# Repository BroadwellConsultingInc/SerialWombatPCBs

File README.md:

# SerialWombatPCBs
Serial Wombat Board Designs and Documentation

This repository holds Eagle PCB designs, gerbers, schematics, and other documentation, code, templates, drawings, etc. related to Serial Wombat brand PCBs.

Serial Wombat is a registered trademark in the United States of Broadwell Consulting Inc.

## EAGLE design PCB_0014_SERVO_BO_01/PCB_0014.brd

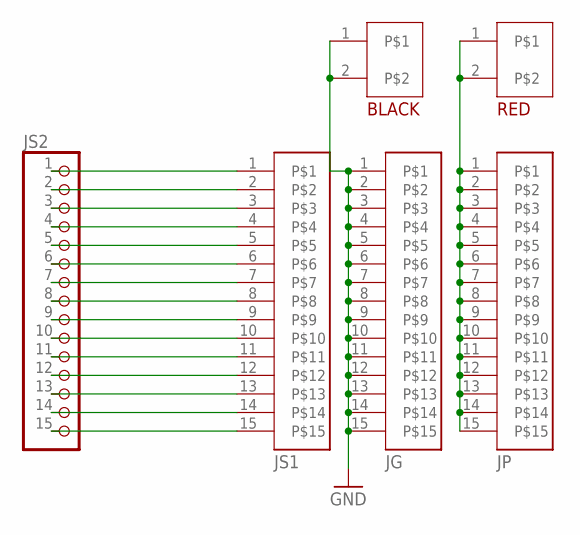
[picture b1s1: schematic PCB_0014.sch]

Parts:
BLACK: SCREWTERMINAL_2PIN; DB125-3.5/3.81
JG: HEADER_15X1; HDRV15W64P254_1X15_3810X254X838B
JP: HEADER_15X1; HDRV15W64P254_1X15_3810X254X838B
JS1: HEADER_15X1; HDRV15W64P254_1X15_3810X254X838B
JS2: PINHD-1X15; 1X15
RED: SCREWTERMINAL_2PIN; DB125-3.5/3.81

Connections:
GND: BLACK.1, BLACK.2, JG.1, JG.2, JG.3, JG.4, JG.5, JG.6, JG.7, JG.8, JG.9, JG.10, JG.11, JG.12, JG.13, JG.14, JG.15
unnamed: JS1.1, JS2.1
unnamed: JS1.2, JS2.2
unnamed: JS1.3, JS2.3
unnamed: JS1.4, JS2.4
unnamed: JS1.5, JS2.5
unnamed: JS1.6, JS2.6
unnamed: JS1.7, JS2.7
unnamed: JS1.8, JS2.8
unnamed: JS1.9, JS2.9
unnamed: JS1.10, JS2.10
unnamed: JS1.11, JS2.11
unnamed: JS1.12, JS2.12
unnamed: JS1.13, JS2.13
unnamed: JS1.14, JS2.14
unnamed: JS1.15, JS2.15
unnamed: JP.1, JP.2, JP.3, JP.4, JP.5, JP.6, JP.7, JP.8, JP.9, JP.10, JP.11, JP.12, JP.13, JP.14, JP.15, RED.1, RED.2

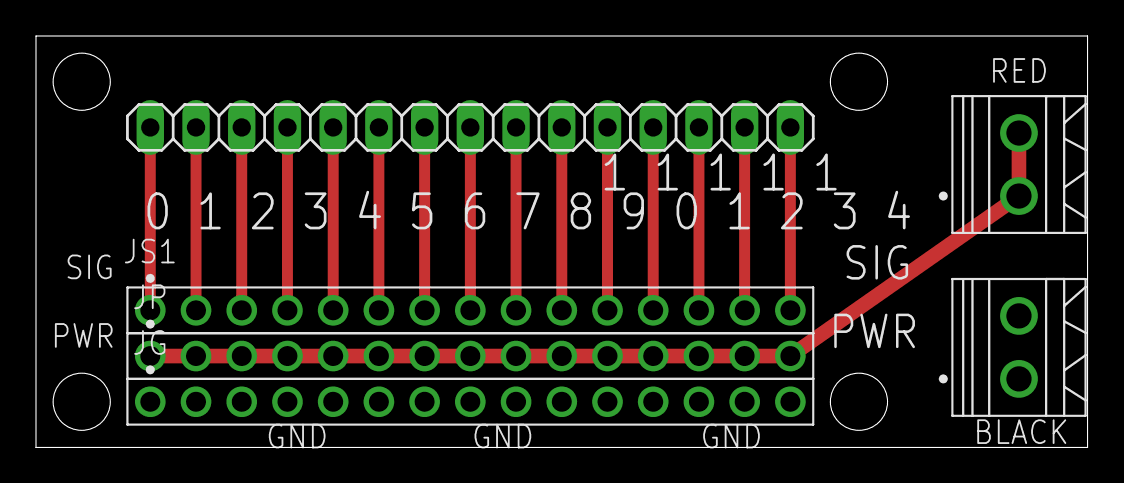
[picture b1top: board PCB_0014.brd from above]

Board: 2 copper layers, 58.4 x 22.9 mm, 6 parts (0 on the bottom side), 17 nets.

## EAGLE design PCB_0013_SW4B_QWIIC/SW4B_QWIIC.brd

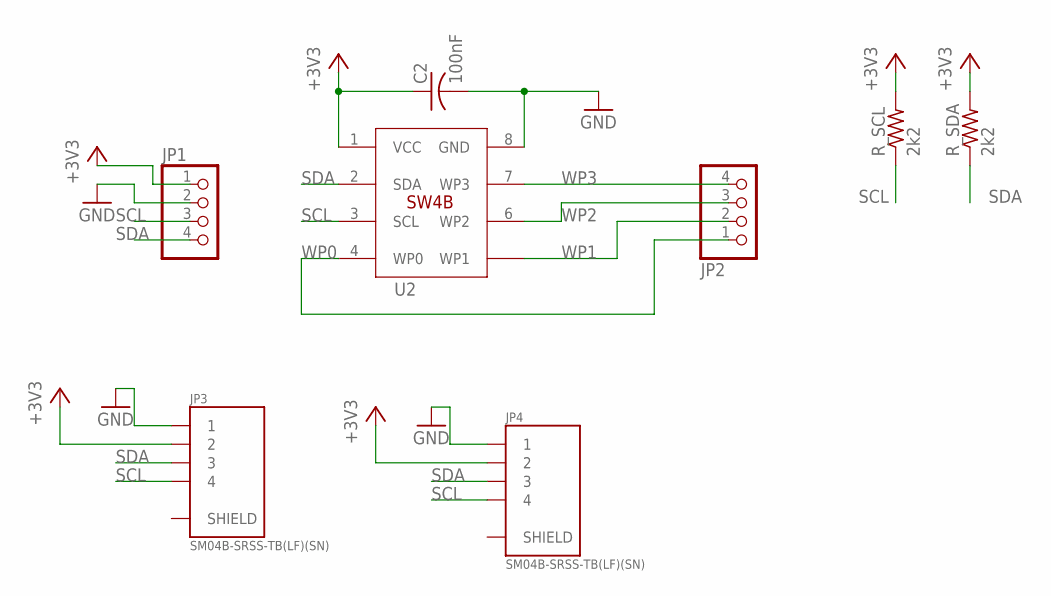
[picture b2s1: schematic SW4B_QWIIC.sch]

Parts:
C2: 100nF; C0603
JP1, JP2: PINHD-1X4; 1X04
JP3, JP4: SM04B-SRSS-TB(LF)(SN); JST_SM04B-SRSS-TB(LF)(SN)
R_SCL: 2k2; R0603
R_SDA: 2k2; R0603
U2: SERIALWOMBAT_4BSOCKETDIP; SW4B_SOCKET

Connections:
+3V3: C2.1, JP1.1, JP3.2, JP4.2, R_SCL.2, R_SDA.2, U2.1 (VCC)
GND: C2.2, JP1.2, JP3.1, JP4.1, U2.8 (GND)
SCL: JP1.3, JP3.4, JP4.4, R_SCL.1, U2.3 (SCL)
SDA: JP1.4, JP3.3, JP4.3, R_SDA.1, U2.2 (SDA)
WP0: JP2.1, U2.4 (WP0)
WP1: JP2.2, U2.5 (WP1)
WP2: JP2.3, U2.6 (WP2)
WP3: JP2.4, U2.7 (WP3)

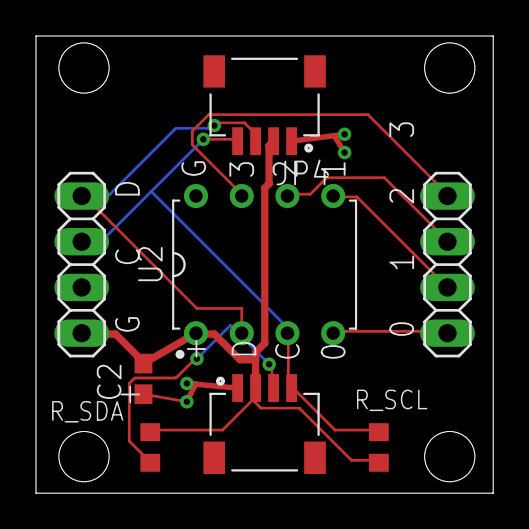
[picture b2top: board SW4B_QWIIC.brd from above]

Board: 2 copper layers, 25.4 x 25.4 mm, 8 parts (0 on the bottom side), 8 nets.

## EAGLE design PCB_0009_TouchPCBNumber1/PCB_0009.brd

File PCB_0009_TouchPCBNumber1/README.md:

# Serial Wombat PCB_0009 Touch PCB

This PCB is designed to work with the Serial Wombat 18AB chip's Cap Touch pin mode.   This PCB provides 9 touch pads which can be connected to the Serial Wombat 18AB chip's analog capable pins.  

See the following for a tutorial on using the Cap Touch pin mode.  Pads on this PCB function essentially the same as a coin covered with tape connected to a wire.  For best results, calibrate each pad as shown in the video after completing your circuit.

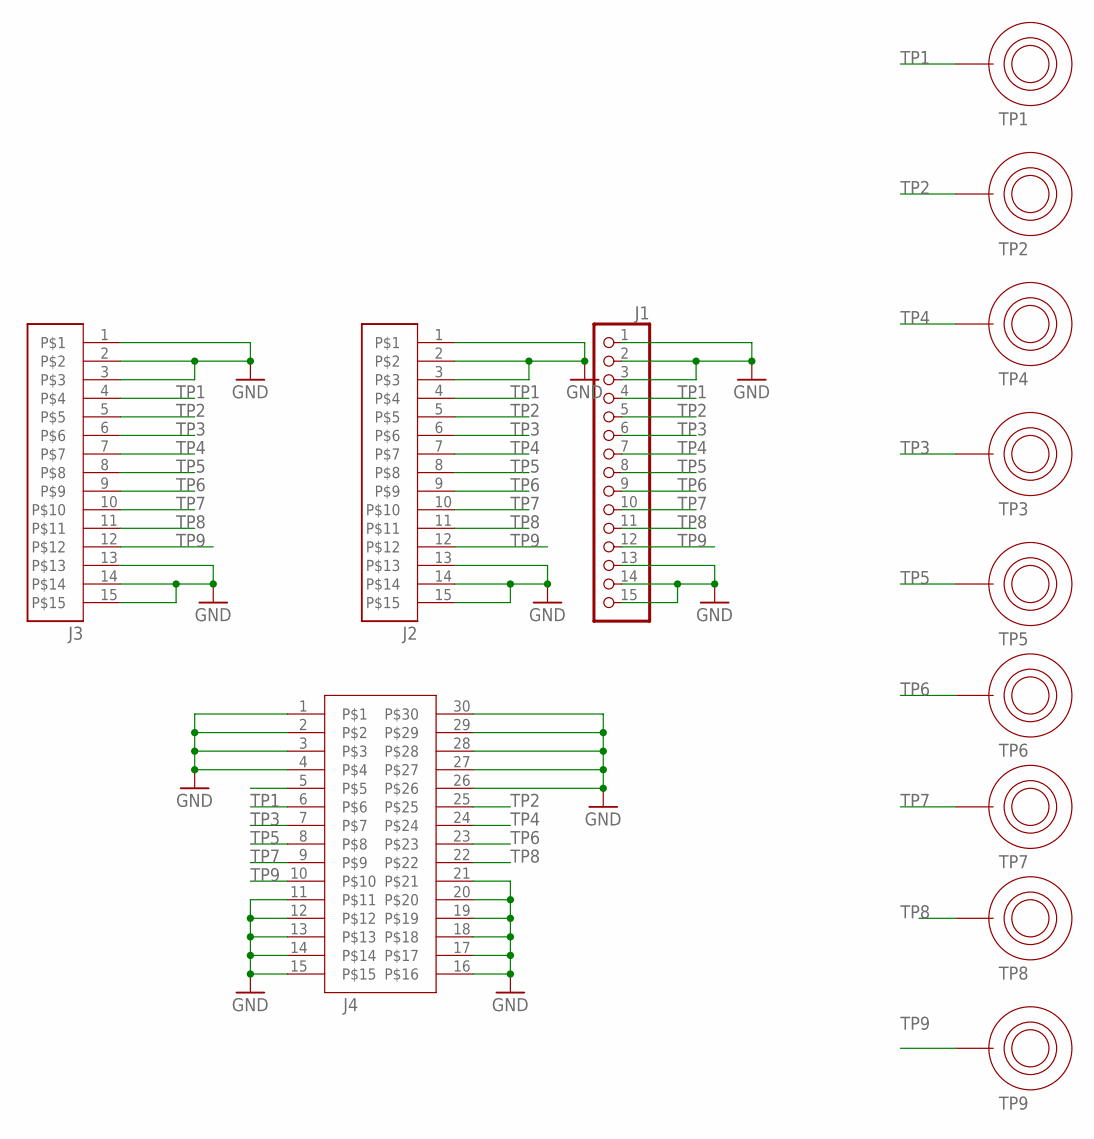
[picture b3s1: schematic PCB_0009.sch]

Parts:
J1: PINHD-1X15; 1X15
J2: HEADER_15X1RA_SMT_HACK; HEADER_1X15_RA_SMT_HACK
J3: HEADER_15X1SMT; HDRV_SMD_15S736P254_1X15_3860X508X965
J4: HEADER_15X2SMT; HDRV_SMD_30S736P254_2X15_3860X508X965
TP1, TP2, TP3, TP4, TP5, TP6, TP7, TP8, TP9: TOUCHPADROUND15MM; TOUCHPAD_ROUND_15MM

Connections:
GND: J1.1, J1.2, J1.3, J1.13, J1.14, J1.15, J2.1, J2.2, J2.3, J2.13, J2.14, J2.15, J3.1, J3.2, J3.3, J3.13, J3.14, J3.15, J4.1, J4.2, J4.3, J4.4, J4.11, J4.12, J4.13, J4.14, J4.15, J4.16, J4.17, J4.18, J4.19, J4.20, J4.21, J4.26, J4.27, J4.28, J4.29, J4.30
TP1: J1.4, J2.4, J3.4, J4.6, TP1.P$1
TP2: J1.5, J2.5, J3.5, J4.25, TP2.P$1
TP3: J1.6, J2.6, J3.6, J4.7, TP3.P$1
TP4: J1.7, J2.7, J3.7, J4.24, TP4.P$1
TP5: J1.8, J2.8, J3.8, J4.8, TP5.P$1
TP6: J1.9, J2.9, J3.9, J4.23, TP6.P$1
TP7: J1.10, J2.10, J3.10, J4.9, TP7.P$1
TP8: J1.11, J2.11, J3.11, J4.22, TP8.P$1
TP9: J1.12, J2.12, J3.12, J4.10, TP9.P$1

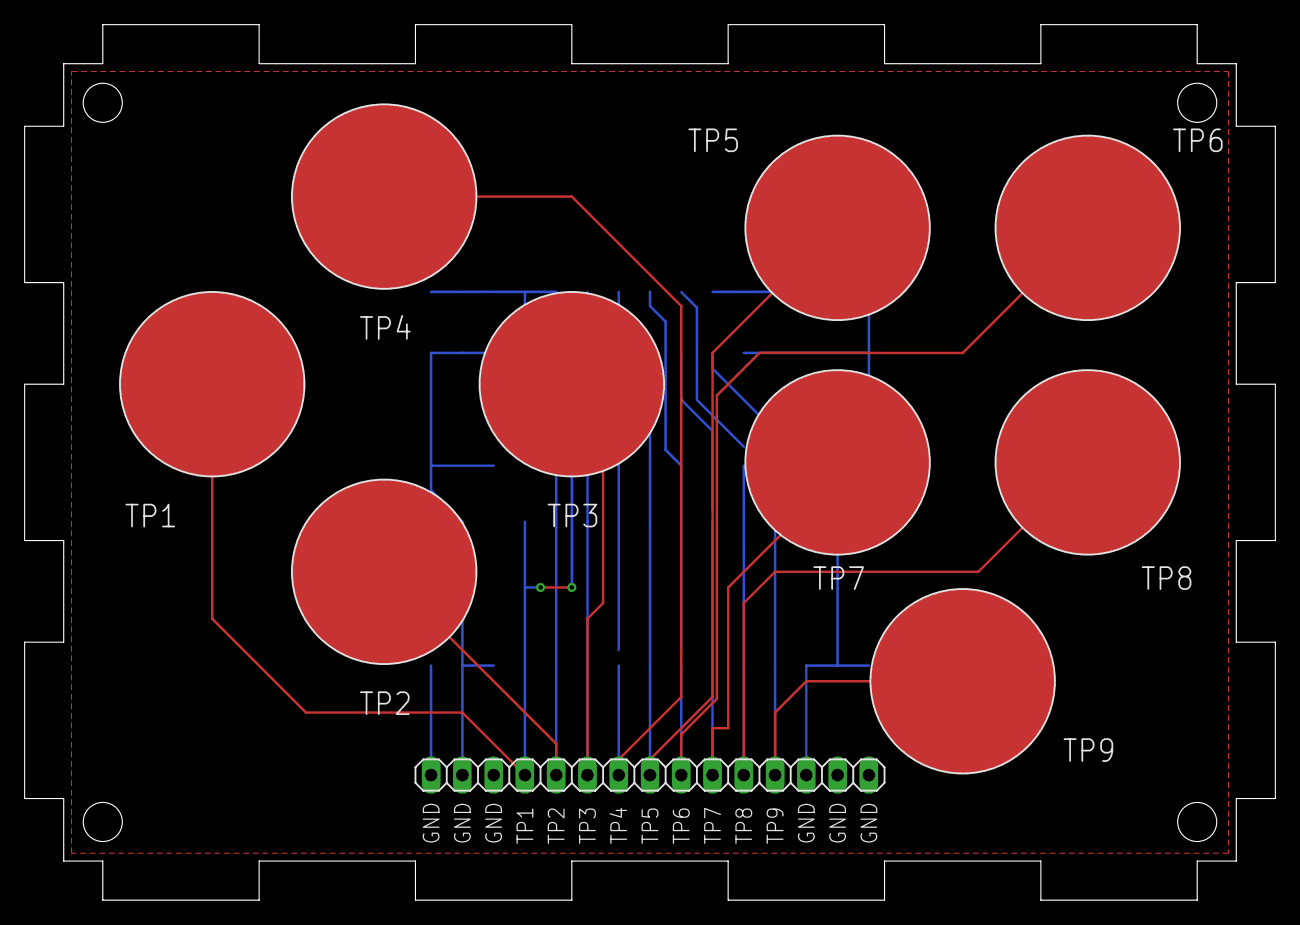
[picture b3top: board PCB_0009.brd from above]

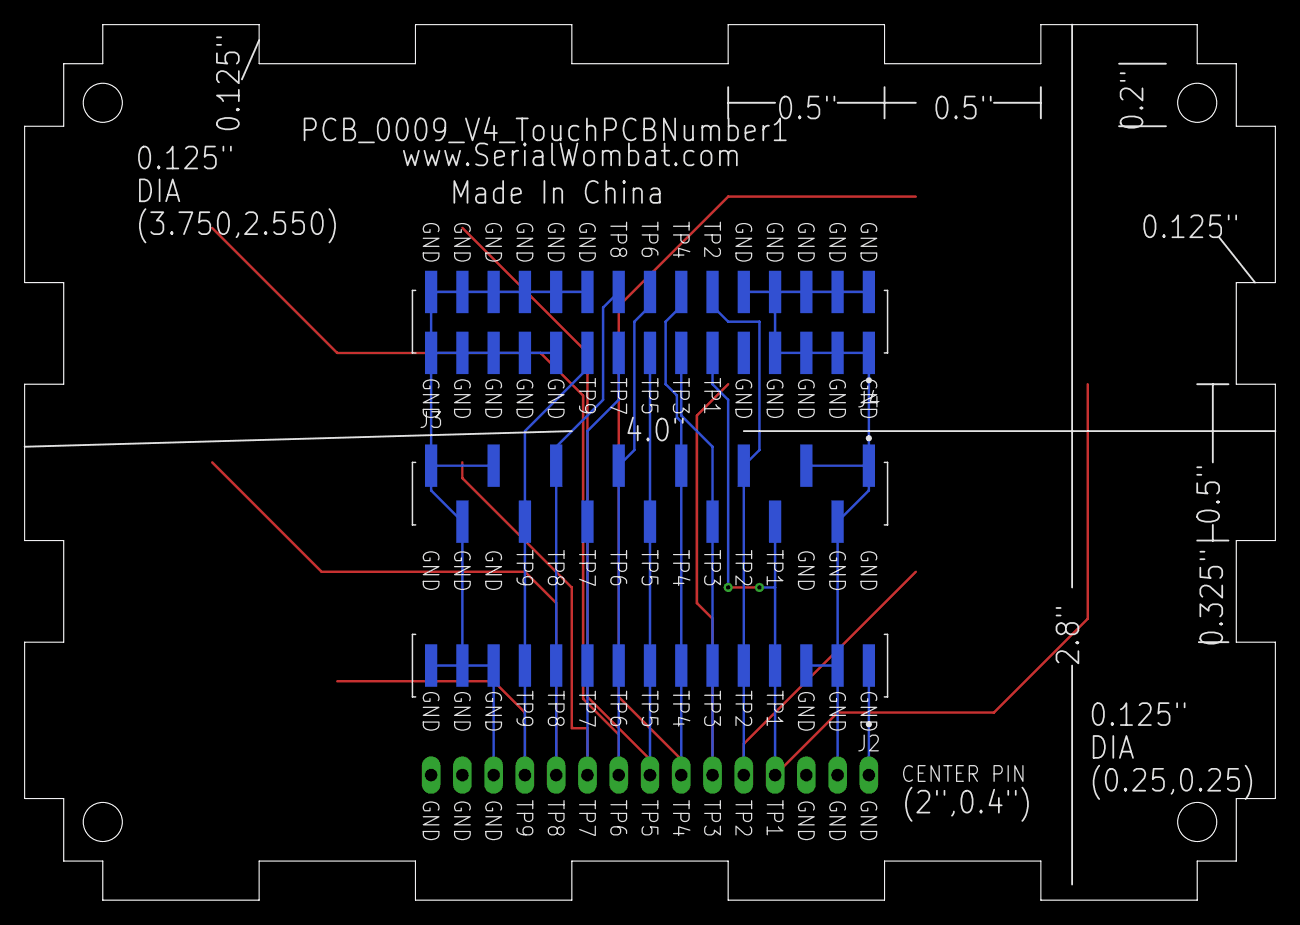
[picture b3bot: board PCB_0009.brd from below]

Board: 2 copper layers, 101.6 x 71.1 mm, 13 parts (3 on the bottom side), 10 nets.

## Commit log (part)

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2022-11-22 Adding PCB_0009 to repository
2022-12-19 Checking in PCB_0009 , PCB_0013, PCB_0014
2022-12-19 Adding Video
2024-09-26 Uploading Rev 3 of PCB0023
2025-03-27 Checking in PCB0029v5
2025-05-15 Checking in PCB0035 Rev 1
